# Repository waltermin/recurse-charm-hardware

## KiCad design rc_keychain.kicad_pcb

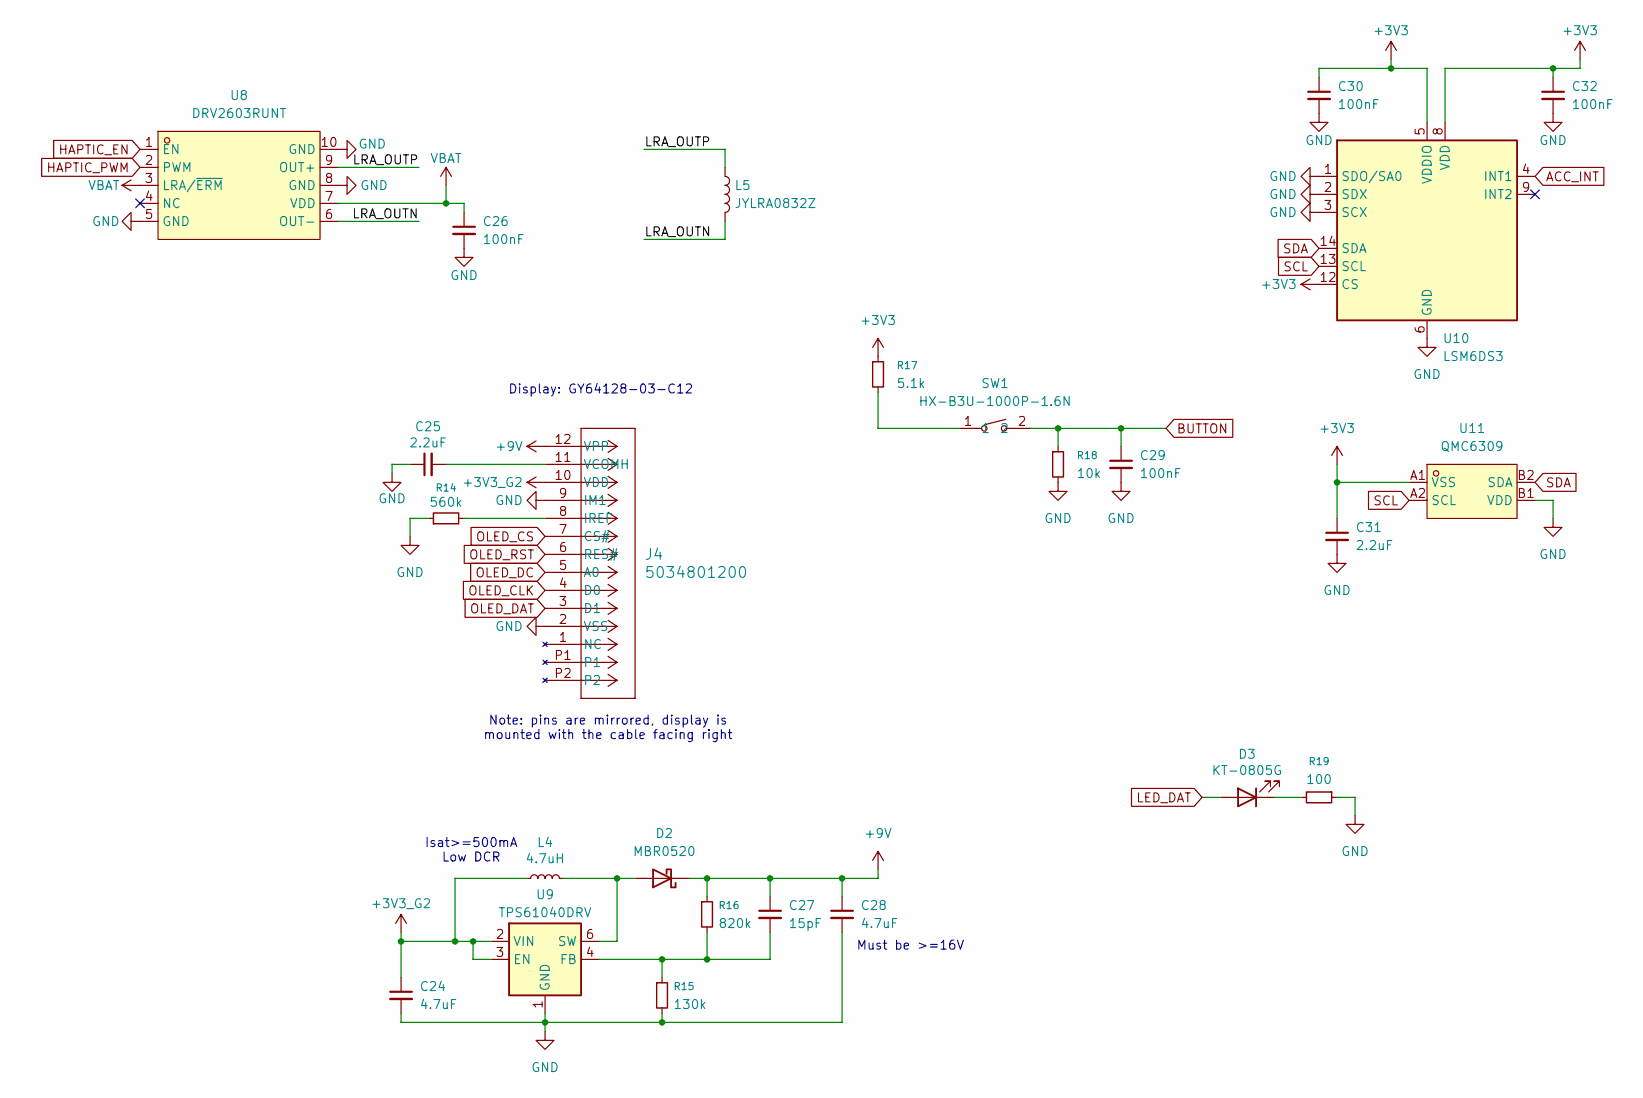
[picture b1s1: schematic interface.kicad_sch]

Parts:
C24: 4.7uF; C_0402_1005Metric; LCSC Part C23733
C25, C31: 2.2uF; C_0402_1005Metric; LCSC Part C12530
C26, C29, C30, C32: 100nF; C_0402_1005Metric; LCSC Part C1525
C27: 15pF; C_0402_1005Metric; LCSC Part C1548
C28: 4.7uF; C_0603_1608Metric; LCSC Part C19666
D2: MBR0520; D_SOD-323; LCSC Part C49238168
D3: KT-0805G; D_0805_2012Metric; LCSC Part C2297
J4: 5034801200; CON_5034801200_MOL; LCSC Part C587969
L4: 4.7uH; IND-SMD_L2.0-W1.6-B; LCSC Part C5832346
L5: JYLRA0832Z; Generic_Solder_Pads_2P
R14: 560k; R_0402_1005Metric; LCSC Part C132339
R15: 130k; R_0402_1005Metric; LCSC Part C93946
R16: 820k; R_0402_1005Metric; LCSC Part C67558
R17: 5.1k; R_0402_1005Metric; LCSC Part C25905
R18: 10k; R_0402_1005Metric; LCSC Part C25744
R19: 100; R_0402_1005Metric; LCSC Part C25076
SW1: HX-B3U-1000P-1.6N; SW-SMD_2P-L3.0-W2.5-LS4.0; MPN HX-B3U-1000P-1.6N; LCSC Part C49234121
U8: DRV2603RUNT; QFN-10_L2.0-W2.0-P0.50-TL; LCSC Part C2150691
U9: TPS61040DRV; WSON-6-1EP_2x2mm_P0.65mm_EP1x1.6mm; LCSC Part C2678534
U10: LSM6DS3; LGA-14_3x2.5mm_P0.5mm_LayoutBorder3x4y; LCSC Part C967633
U11: QMC6309; X1-WLB0808-4_L0.8-W0.8-P0.40-TL; MPN QMC6309; LCSC Part C5439871

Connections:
+3V3: C30.1, C31.1, C32.1, R17.1, U10.5 (VDDIO), U10.8 (VDD), U10.12 (CS), U11.A1 (VSS); also elsewhere on the board
+3V3_G2: C24.1, J4.10 (VDD), L4.1, U9.2 (VIN), U9.3 (EN); also elsewhere on the board
+9V: C27.1, C28.1, D2.1 (K), J4.12 (VPP), R16.1
/interface/LRA_OUTN: L5.2, U8.6 (OUT-)
/interface/LRA_OUTP: L5.1, U8.9 (OUT+)
ACC_INT: U10.4 (INT1); also elsewhere on the board
BUTTON: C29.1, R18.1, SW1.2; also elsewhere on the board
GND: C24.2, C25.1, C26.2, C28.2, C29.2, C30.2, C31.2, C32.2, J4.2 (VSS), J4.9 (IM1), R14.1, R15.2, R18.2, R19.1, U8.5 (GND), U8.8 (GND), U8.10 (GND), U9.1 (GND), U10.1 (SDO/SA0), U10.2 (SDX), U10.3 (SCX), U10.6 (GND), U10.7 (GND), U11.B1 (VDD); also elsewhere on the board
HAPTIC_EN: U8.1 (EN); also elsewhere on the board
HAPTIC_PWM: U8.2 (PWM); also elsewhere on the board
LED_DAT: D3.2 (A); also elsewhere on the board
unnamed: D2.2 (A), L4.2, U9.6 (SW)
unnamed: D3.1 (K), R19.2
unnamed: J4.8 (IREF), R14.2
unnamed: C25.2, J4.11 (VCOMH)
unnamed: R17.2, SW1.1
unnamed: C27.2, R15.1, R16.2, U9.4 (FB)
OLED_CLK: J4.4 (D0); also elsewhere on the board
OLED_CS: J4.7 (CS#); also elsewhere on the board
OLED_DAT: J4.3 (D1); also elsewhere on the board
OLED_DC: J4.5 (A0); also elsewhere on the board
OLED_RST: J4.6 (RES#); also elsewhere on the board
SCL: U10.13 (SCL), U11.A2 (SCL); also elsewhere on the board
SDA: U10.14 (SDA), U11.B2 (SDA); also elsewhere on the board
VBAT: C26.1, U8.3 (LRA/~ERM), U8.7 (VDD); also elsewhere on the board

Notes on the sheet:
Display: GY64128-03-C12
Isat>=500mA Low DCR
Note: pins are mirrored, display is mounted with the cable facing right
Must be >=16V

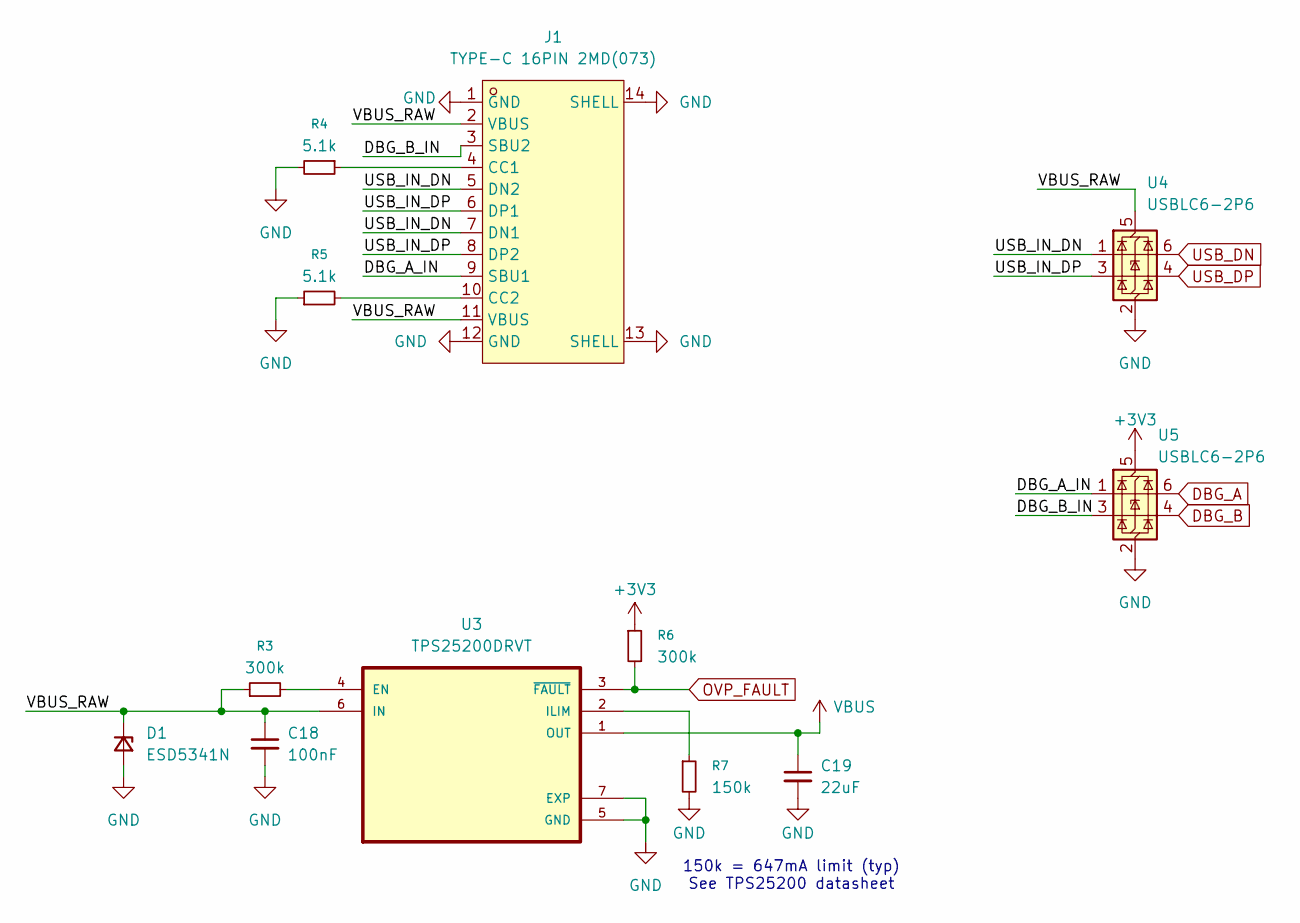
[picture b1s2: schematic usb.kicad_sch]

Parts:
C18: 100nF; C_0402_1005Metric; LCSC Part C1525
C19: 22uF; C_0402_1005Metric; LCSC Part C47339
D1: ESD5341N; D_SOD-882; LCSC Part C3021106
J1: TYPE-C 16PIN 2MD(073); USB-C-SMD_TYPE-C-6PIN-2MD-073; LCSC Part C2765186
R3, R6: 300k; R_0402_1005Metric; LCSC Part C25774
R4, R5: 5.1k; R_0402_1005Metric; LCSC Part C25905
R7: 150k; R_0402_1005Metric; LCSC Part C2909320
U3: TPS25200DRVT; SON65P200X200X80-7N; DigiKey_Part_Number 296-37760-1-ND
U4, U5: USBLC6-2P6; SOT-666; LCSC Part C2827693

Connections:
+3V3: R6.1, U5.5 (VBUS); also elsewhere on the board
/usb/DBG_A_IN: J1.9 (SBU1), U5.1 (I/O1)
/usb/DBG_B_IN: J1.3 (SBU2), U5.3 (I/O2)
/usb/USB_IN_DN: J1.5 (DN2), J1.7 (DN1), U4.1 (I/O1)
/usb/USB_IN_DP: J1.6 (DP1), J1.8 (DP2), U4.3 (I/O2)
/usb/VBUS_RAW: C18.1, D1.1 (K), J1.2 (VBUS), J1.11 (VBUS), R3.1, U3.6 (IN), U4.5 (VBUS)
DBG_A: U5.6 (I/O1); also elsewhere on the board
DBG_B: U5.4 (I/O2); also elsewhere on the board
GND: C18.2, C19.2, D1.2 (A), J1.1 (GND), J1.12 (GND), J1.13 (SHELL), J1.14 (SHELL), R4.2, R5.1, R7.2, U3.5 (GND), U3.7 (EXP), U4.2 (GND), U5.2 (GND); also elsewhere on the board
unnamed: J1.4 (CC1), R4.1
unnamed: J1.10 (CC2), R5.2
unnamed: R3.2, U3.4 (EN)
unnamed: R7.1, U3.2 (ILIM)
OVP_FAULT: R6.2, U3.3 (~FAULT)
USB_DN: U4.6 (I/O1); also elsewhere on the board
USB_DP: U4.4 (I/O2); also elsewhere on the board
VBUS: C19.1, U3.1 (OUT); also elsewhere on the board

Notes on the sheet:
150k = 647mA limit (typ) See TPS25200 datasheet

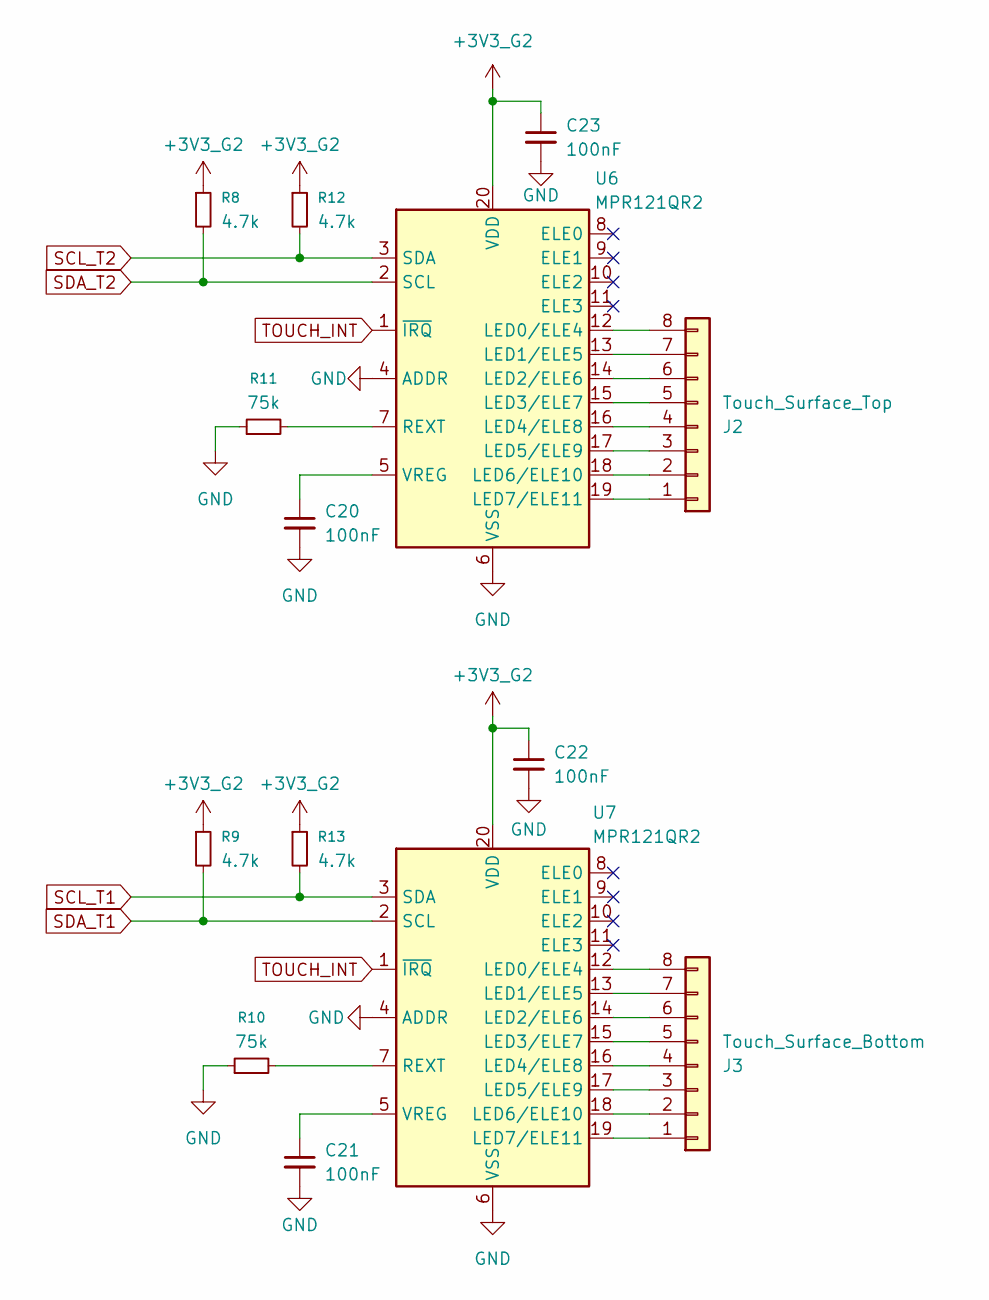
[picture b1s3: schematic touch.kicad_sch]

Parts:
C20, C21, C22, C23: 100nF; C_0402_1005Metric; LCSC Part C1525
J2: Touch_Surface_Top; Touch_Surface_8_Pad_Slim
J3: Touch_Surface_Bottom; Touch_Surface_8_Pad_Slim
R8, R9, R12, R13: 4.7k; R_0402_1005Metric; LCSC Part C25900
R10, R11: 75k; R_0402_1005Metric; LCSC Part C25798
U6, U7: MPR121QR2; UQFN-20_3x3mm_P0.4mm; LCSC Part C91322

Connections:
+3V3_G2: C22.1, C23.1, R8.1, R9.1, R12.1, R13.1, U6.20 (VDD), U7.20 (VDD); also elsewhere on the board
GND: C20.2, C21.2, C22.2, C23.2, R10.1, R11.1, U6.4 (ADDR), U6.6 (VSS), U7.4 (ADDR), U7.6 (VSS); also elsewhere on the board
unnamed: J2.1, U6.19 (LED7/ELE11)
unnamed: J2.2, U6.18 (LED6/ELE10)
unnamed: J2.3, U6.17 (LED5/ELE9)
unnamed: J2.4, U6.16 (LED4/ELE8)
unnamed: J2.5, U6.15 (LED3/ELE7)
unnamed: J2.6, U6.14 (LED2/ELE6)
unnamed: J2.7, U6.13 (LED1/ELE5)
unnamed: J2.8, U6.12 (LED0/ELE4)
unnamed: J3.1, U7.19 (LED7/ELE11)
unnamed: J3.2, U7.18 (LED6/ELE10)
unnamed: J3.3, U7.17 (LED5/ELE9)
unnamed: J3.4, U7.16 (LED4/ELE8)
unnamed: J3.5, U7.15 (LED3/ELE7)
unnamed: J3.6, U7.14 (LED2/ELE6)
unnamed: J3.7, U7.13 (LED1/ELE5)
unnamed: J3.8, U7.12 (LED0/ELE4)
unnamed: R11.2, U6.7 (REXT)
unnamed: C20.1, U6.5 (VREG)
unnamed: R10.2, U7.7 (REXT)
unnamed: C21.1, U7.5 (VREG)
SCL_T1: R13.2, U7.3 (SDA); also elsewhere on the board
SCL_T2: R12.2, U6.3 (SDA); also elsewhere on the board
SDA_T1: R9.2, U7.2 (SCL); also elsewhere on the board
SDA_T2: R8.2, U6.2 (SCL); also elsewhere on the board
TOUCH_INT: U6.1 (~IRQ), U7.1 (~IRQ); also elsewhere on the board

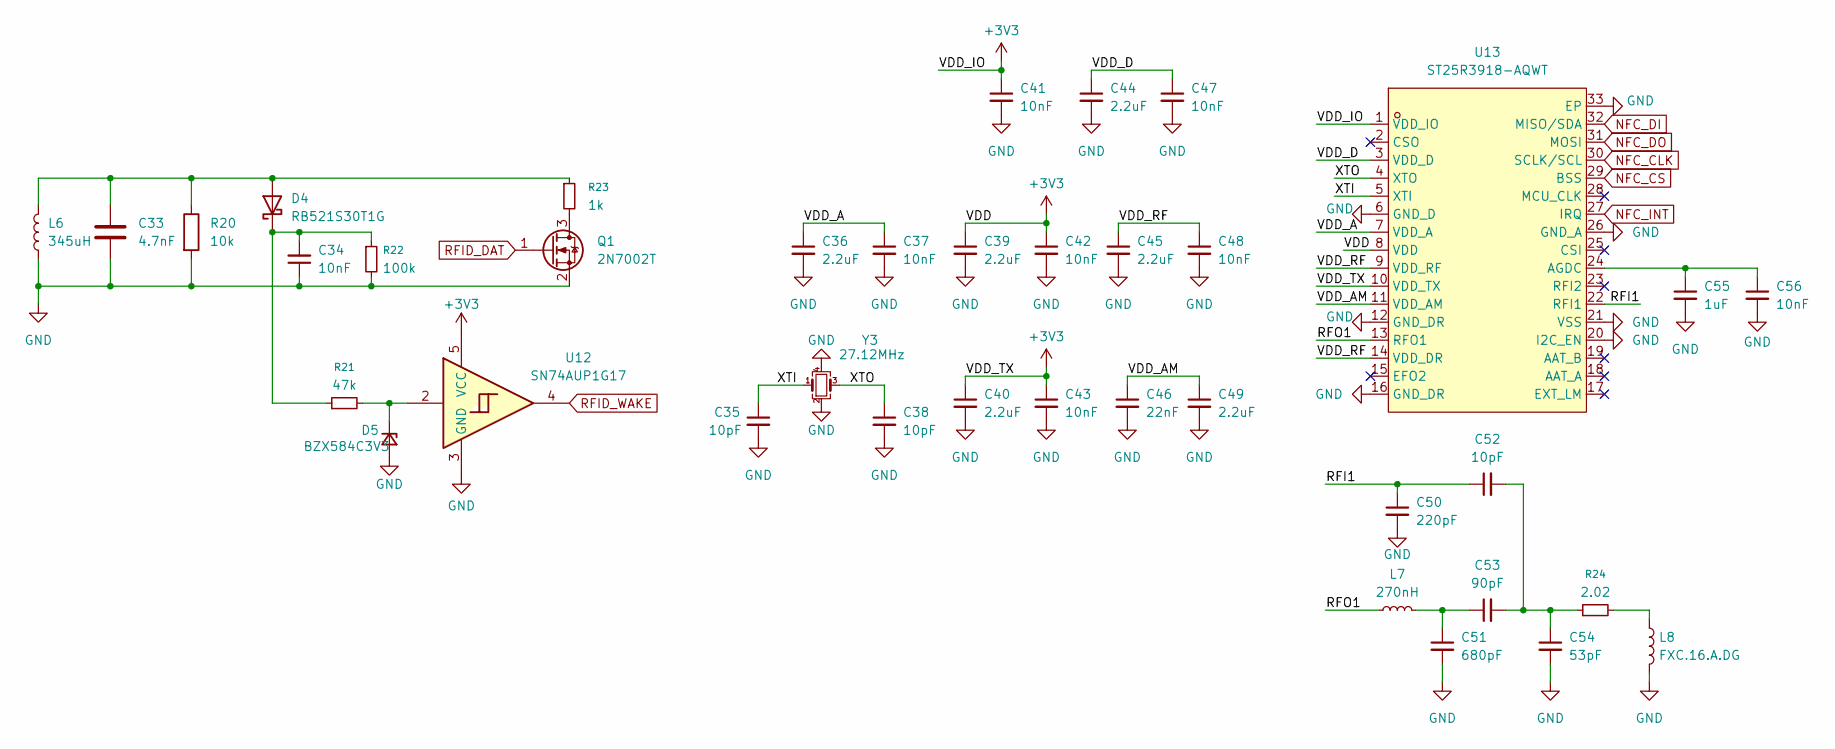
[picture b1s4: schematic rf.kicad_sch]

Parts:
C33: 4.7nF; C_0402_1005Metric; LCSC Part C1538
C34: 10nF; C_0402_1005Metric; LCSC Part C15195
C35, C38, C52: 10pF; C_0402_1005Metric; LCSC Part C32949
C36, C39, C40, C44, C45, C49: 2.2uF; C_0201_0603Metric; LCSC Part C335106
C37, C41, C42, C43, C47, C48, C56: 10nF; C_0201_0603Metric; LCSC Part C272853
C46: 22nF; C_0201_0603Metric; LCSC Part C668343
C50: 220pF; C_0402_1005Metric; LCSC Part C71693
C51: 680pF; C_0402_1005Metric; LCSC Part C307451
C53: 90pF; C_0402_1005Metric; LCSC Part C1864488
C54: 53pF; C_0402_1005Metric; LCSC Part C541437
C55: 1uF; C_0201_0603Metric; LCSC Part C53067
D4: RB521S30T1G; D_SOD-523; LCSC Part C145179
D5: BZX584C3V3; D_SOD-523; LCSC Part C19077462
L6: 345uH; Generic_Solder_Pads_2P
L7: 270nH; L_0603_1608Metric; LCSC Part C2041707
L8: FXC.16.A.DG; Generic_Solder_Pads_2P
Q1: 2N7002T; SOT-523; LCSC Part C2844731
R20: 10k; R_0402_1005Metric; LCSC Part C25744
R21: 47k; R_0402_1005Metric; LCSC Part C25792
R22: 100k; R_0402_1005Metric; LCSC Part C25741
R23: 1k; R_0402_1005Metric; LCSC Part C11702
R24: 2.02; R_0402_1005Metric; LCSC Part C2998051
U12: SN74AUP1G17; Diodes_SOT-553; LCSC Part C49374609
U13: ST25R3918-AQWT; QFN-32_L5.0-W5.0-P0.50-TL-EP3.5; LCSC Part C3304617
Y3: 27.12MHz; Crystal_SMD_2016-4Pin_2.0x1.6mm; LCSC Part C7301953

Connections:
+3V3: C39.1, C40.1, C41.1, C42.1, C43.1, U12.5 (VCC), U13.1 (VDD_IO), U13.8 (VDD), U13.10 (VDD_TX); also elsewhere on the board
/rf/RFI1: C50.1, C52.1, U13.22 (RFI1)
/rf/RFO1: L7.1, U13.13 (RFO1)
/rf/VDD_A: C36.1, C37.1, U13.7 (VDD_A)
/rf/VDD_AM: C46.1, C49.1, U13.11 (VDD_AM)
/rf/VDD_D: C44.1, C47.1, U13.3 (VDD_D)
/rf/VDD_RF: C45.1, C48.1, U13.9 (VDD_RF), U13.14 (VDD_DR)
/rf/XTI: C35.1, U13.5 (XTI), Y3.1
/rf/XTO: C38.1, U13.4 (XTO), Y3.3
GND: C33.2, C34.1, C35.2, C36.2, C37.2, C38.2, C39.2, C40.2, C41.2, C42.2, C43.2, C44.2, C45.2, C46.2, C47.2, C48.2, C49.2, C50.2, C51.2, C54.2, C55.2, C56.2, D5.2 (A), L6.1, L8.2, Q1.2 (S), R20.2, R22.2, U12.3 (GND), U13.6 (GND_D), U13.12 (GND_DR), U13.16 (GND_DR), U13.20 (I2C_EN), U13.21 (VSS), U13.26 (GND_A), U13.33 (EP), Y3.2, Y3.4; also elsewhere on the board
NFC_CLK: U13.30 (SCLK/SCL); also elsewhere on the board
NFC_CS: U13.29 (BSS); also elsewhere on the board
NFC_DI: U13.32 (MISO/SDA); also elsewhere on the board
NFC_DO: U13.31 (MOSI); also elsewhere on the board
NFC_INT: U13.27 (IRQ); also elsewhere on the board
unnamed: C51.1, C53.1, L7.2
unnamed: C52.2, C53.2, C54.1, R24.1
unnamed: C33.1, D4.2 (A), L6.2, R20.1, R23.1
unnamed: C34.2, D4.1 (K), R21.1, R22.1
unnamed: D5.1 (K), R21.2, U12.2
unnamed: L8.1, R24.2
unnamed: Q1.3 (D), R23.2
unnamed: C55.1, C56.1, U13.24 (AGDC)
RFID_DAT: Q1.1 (G); also elsewhere on the board
RFID_WAKE: U12.4; also elsewhere on the board

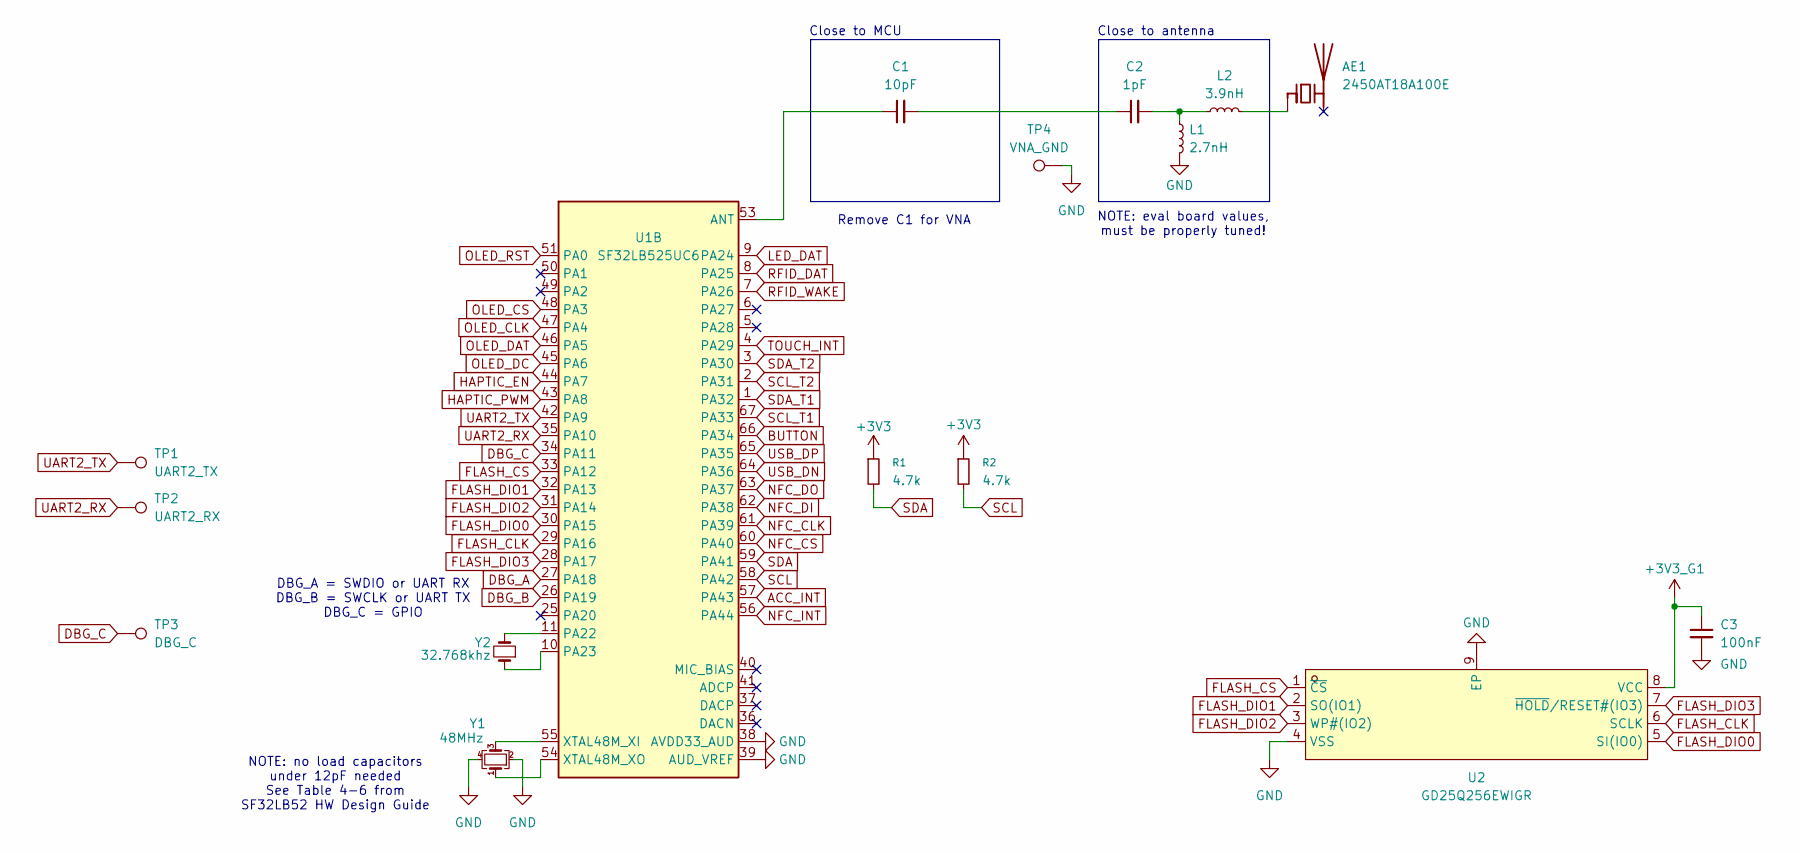
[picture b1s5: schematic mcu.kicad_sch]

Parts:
AE1: 2450AT18A100E; R_1206_3216Metric; LCSC Part C89334
C1: 10pF; C_0402_1005Metric; LCSC Part C32949
C2: 1pF; C_0603_1608Metric; LCSC Part C307493
C3: 100nF; C_0402_1005Metric; LCSC Part C1525
L1: 2.7nH; L_0603_1608Metric; LCSC Part C412027
L2: 3.9nH; L_0603_1608Metric; LCSC Part C13818
R1, R2: 4.7k; R_0402_1005Metric; LCSC Part C25900
TP1: UART2_TX; TestPoint_Pad_D1.0mm
TP2: UART2_RX; TestPoint_Pad_D1.0mm
TP3: DBG_C; TestPoint_Pad_D1.0mm
TP4: VNA_GND; TestPoint_Pad_D1.0mm
U1: SF32LB525UC6; ArtInChip_QFN-68-1EP_7x7mm_P0.35mm_EP5.49x5.49mm; LCSC Part C47355842
U2: GD25Q256EWIGR; WSON-8_L6.0-W5.0-P1.27-TL-EP; LCSC Part C6564321
Y1: 48MHz; Crystal_SMD_2016-4Pin_2.0x1.6mm; LCSC Part C49363531
Y2: 32.768khz; Crystal_SMD_2012-2Pin_2.0x1.2mm; LCSC Part C99009

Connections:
+3V3: R1.1, R2.1; also elsewhere on the board
+3V3_G1: C3.1, U2.8 (VCC); also elsewhere on the board
ACC_INT: U1.57 (PA43); also elsewhere on the board
BUTTON: U1.66 (PA34); also elsewhere on the board
DBG_A: U1.27 (PA18); also elsewhere on the board
DBG_B: U1.26 (PA19); also elsewhere on the board
DBG_C: TP3.1, U1.34 (PA11)
FLASH_CLK: U1.29 (PA16), U2.6 (SCLK)
FLASH_CS: U1.33 (PA12), U2.1 (~CS)
FLASH_DIO0: U1.30 (PA15), U2.5 (SI(IO0))
FLASH_DIO1: U1.32 (PA13), U2.2 (SO(IO1))
FLASH_DIO2: U1.31 (PA14), U2.3 (WP#(IO2))
FLASH_DIO3: U1.28 (PA17), U2.7 (~HOLD/RESET#(IO3))
GND: C3.2, L1.2, TP4.1, U1.38 (AVDD33_AUD), U1.39 (AUD_VREF), U2.4 (VSS), U2.9 (EP), Y1.2, Y1.4; also elsewhere on the board
HAPTIC_EN: U1.44 (PA7); also elsewhere on the board
HAPTIC_PWM: U1.43 (PA8); also elsewhere on the board
LED_DAT: U1.9 (PA24); also elsewhere on the board
NFC_CLK: U1.61 (PA39); also elsewhere on the board
NFC_CS: U1.60 (PA40); also elsewhere on the board
NFC_DI: U1.62 (PA38); also elsewhere on the board
NFC_DO: U1.63 (PA37); also elsewhere on the board
NFC_INT: U1.56 (PA44); also elsewhere on the board
unnamed: AE1.1 (FEED), L2.2
unnamed: C1.2, C2.1
unnamed: C2.2, L1.1, L2.1
unnamed: C1.1, U1.53 (ANT)
unnamed: U1.11 (PA22), Y2.2
unnamed: U1.10 (PA23), Y2.1
unnamed: U1.55 (XTAL48M_XI), Y1.3
unnamed: U1.54 (XTAL48M_XO), Y1.1
OLED_CLK: U1.47 (PA4); also elsewhere on the board
OLED_CS: U1.48 (PA3); also elsewhere on the board
OLED_DAT: U1.46 (PA5); also elsewhere on the board
OLED_DC: U1.45 (PA6); also elsewhere on the board
OLED_RST: U1.51 (PA0); also elsewhere on the board
RFID_DAT: U1.8 (PA25); also elsewhere on the board
RFID_WAKE: U1.7 (PA26); also elsewhere on the board
SCL: R2.2, U1.58 (PA42); also elsewhere on the board
SCL_T1: U1.67 (PA33); also elsewhere on the board
SCL_T2: U1.2 (PA31); also elsewhere on the board
SDA: R1.2, U1.59 (PA41); also elsewhere on the board
SDA_T1: U1.1 (PA32); also elsewhere on the board
SDA_T2: U1.3 (PA30); also elsewhere on the board
TOUCH_INT: U1.4 (PA29); also elsewhere on the board
UART2_RX: TP2.1, U1.35 (PA10)
UART2_TX: TP1.1, U1.42 (PA9)
USB_DN: U1.64 (PA36); also elsewhere on the board
USB_DP: U1.65 (PA35); also elsewhere on the board

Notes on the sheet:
NOTE: eval board values, must be properly tuned!
Remove C1 for VNA
Close to MCU
DBG_A = SWDIO or UART RX DBG_B = SWCLK or UART TX DBG_C = GPIO
NOTE: no load capacitors under 12pF needed See Table 4-6 from SF32LB52 HW Design Guide
Close to antenna

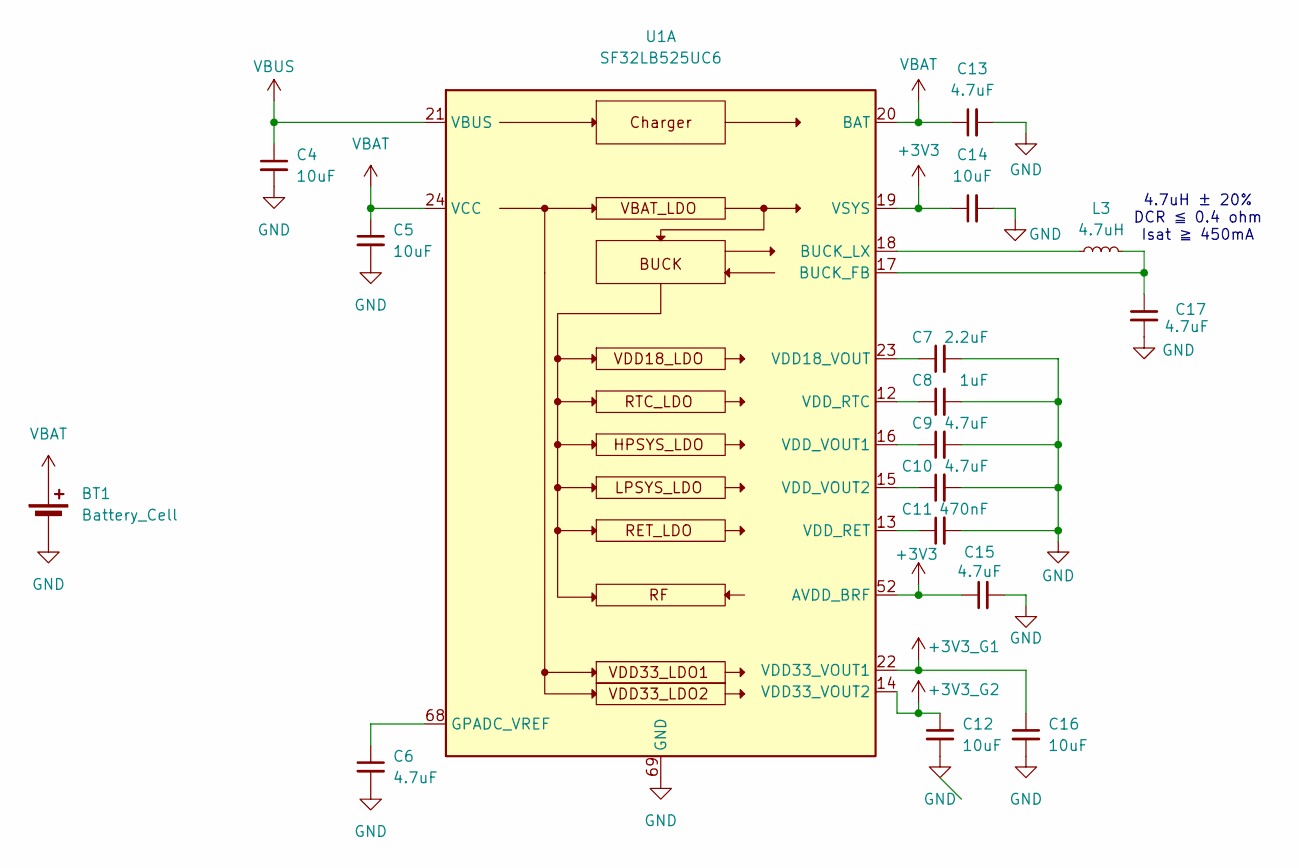
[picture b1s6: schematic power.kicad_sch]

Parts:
BT1: Battery_Cell; Generic_Solder_Pads_2P
C4, C5, C12, C14, C16: 10uF; C_0402_1005Metric; LCSC Part C15525
C6, C9, C10, C15: 4.7uF; C_0201_0603Metric; LCSC Part C335103
C7: 2.2uF; C_0201_0603Metric; LCSC Part C335106
C8: 1uF; C_0201_0603Metric; LCSC Part C53067
C11: 470nF; C_0201_0603Metric; LCSC Part C85926
C13, C17: 4.7uF; C_0402_1005Metric; LCSC Part C23733
L3: 4.7uH; L_0402_1005Metric; LCSC Part C86065
U1: SF32LB525UC6; ArtInChip_QFN-68-1EP_7x7mm_P0.35mm_EP5.49x5.49mm; LCSC Part C47355842

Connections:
+3V3: C14.1, C15.1, U1.19 (VSYS), U1.52 (AVDD_BRF); also elsewhere on the board
+3V3_G1: C16.1, U1.22 (VDD33_VOUT1); also elsewhere on the board
+3V3_G2: C12.1, U1.14 (VDD33_VOUT2); also elsewhere on the board
GND: BT1.2 (-), C4.2, C5.2, C6.2, C7.2, C8.2, C9.2, C10.2, C11.2, C12.2, C13.2, C14.2, C15.2, C16.2, C17.2, U1.69 (GND); also elsewhere on the board
unnamed: C17.1, L3.2, U1.17 (BUCK_FB)
unnamed: L3.1, U1.18 (BUCK_LX)
unnamed: C6.1, U1.68 (GPADC_VREF)
unnamed: C7.1, U1.23 (VDD18_VOUT)
unnamed: C11.1, U1.13 (VDD_RET)
unnamed: C8.1, U1.12 (VDD_RTC)
unnamed: C9.1, U1.16 (VDD_VOUT1)
unnamed: C10.1, U1.15 (VDD_VOUT2)
VBAT: BT1.1 (+), C5.1, C13.1, U1.20 (BAT), U1.24 (VCC); also elsewhere on the board
VBUS: C4.1, U1.21 (VBUS); also elsewhere on the board

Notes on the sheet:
4.7uH ± 20% DCR ≦ 0.4 ohm Isat ≧ 450mA

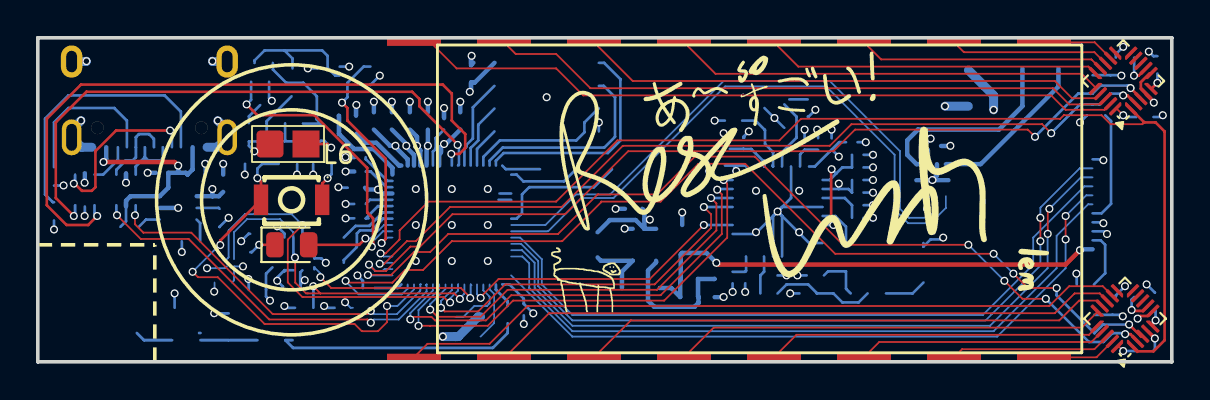
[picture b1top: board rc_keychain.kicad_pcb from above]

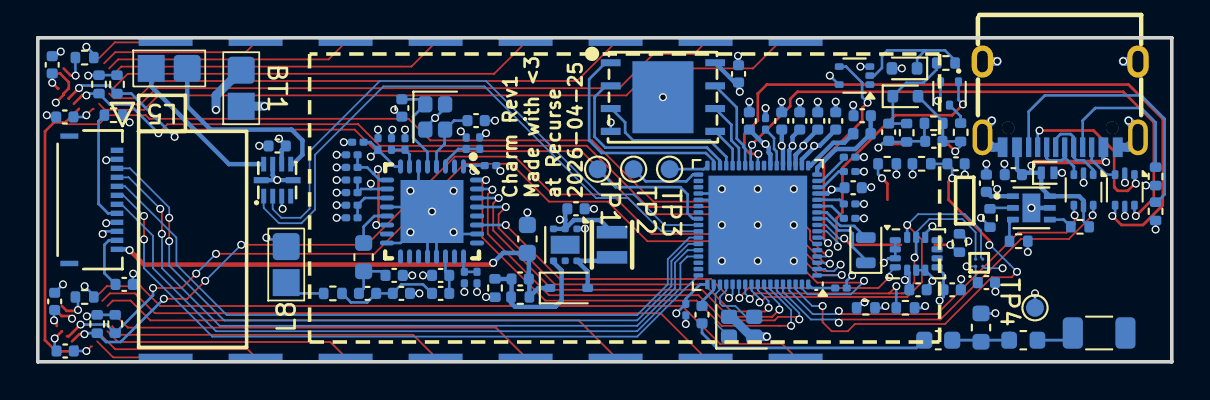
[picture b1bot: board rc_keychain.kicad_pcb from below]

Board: 4 copper layers, 63.0 x 18.0 mm, 121 parts (114 on the bottom side), 114 nets.

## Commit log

2026-03-03 save progress before refactor
2026-03-05 progress dump
2026-03-07 finish up everything but nfc
2026-03-10 progress
2026-03-11 push changes before removing fuel gauge
2026-03-13 hopefully final schematic before splitting out
2026-03-14 final review, fixes, cleanup
2026-03-14 prepare schematic for devboard
2026-03-16 huge progress on bentoboard, schematic fixes
2026-03-17 rev1 done hopefully
2026-03-17 fixups before manufacturing pt1
2026-03-17 fixups before manufacturing pt2
2026-03-18 final shipped rev1 bentoboard
2026-04-12 oops fix: reversed diodes
2026-04-12 oops fix: accelerometer
2026-04-12 remove all jumpers
2026-04-12 revise some decoupling caps to be 0201
2026-04-12 layout progress
2026-04-19 progress 2
2026-04-19 progress 3
2026-04-19 progress 4
2026-04-19 progress 5
2026-04-21 progress before minor redesign
2026-04-21 progress before stepping
2026-04-21 progress before restarting bigtime
2026-04-22 commit before not redesigning
2026-04-22 progress before finagling
2026-04-22 progress mid-finagling
2026-04-23 huge progress
2026-04-23 first draft of final board
2026-04-25 final fixups before prod
